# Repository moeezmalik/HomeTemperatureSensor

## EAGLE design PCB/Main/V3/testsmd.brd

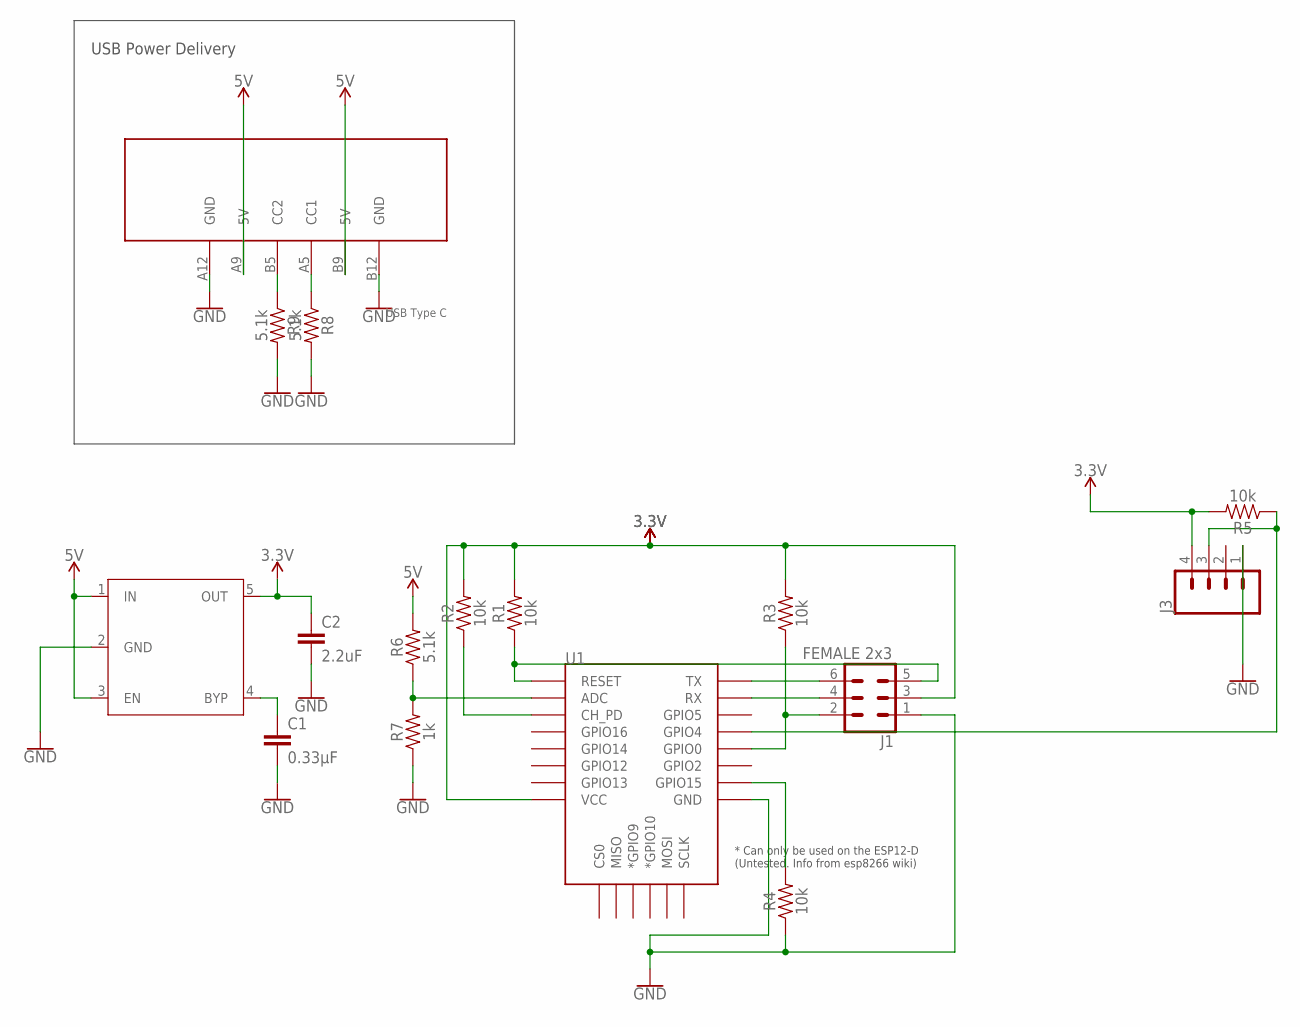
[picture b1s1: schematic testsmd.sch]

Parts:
C1: 0.33µF; 0805
C2: 2.2uF; 1206
J1: FEMALE 2x3; 2X3
J3: CONN_04; 1X04
R1, R2, R3, R4, R5: 10k; 0805
R6, R8, R9: 5.1k; 0805
R7: 1k; 0805
U1: ESP12ESMD; ESP12E-SMD
U$1: MIC5219; SOT95P280X145-5N
U$3: USBC6PIN

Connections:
3.3V: C2.1, J1.3, J3.4, R1.2, R2.2, R3.2, R5.2, U1.VCC, U$1.5 (OUT)
5V: R6.2, U$1.1 (IN), U$1.3 (EN), U$3.A9 (5V), U$3.B9 (5V)
GND: C1.2, C2.2, J1.1, J3.1, R4.1, R7.1, R8.2, R9.2, U1.GND, U$1.2 (GND), U$3.A12 (GND), U$3.B12 (GND)
unnamed: R4.2, U1.GPIO15
unnamed: J1.6, U1.TXD0 (TX)
unnamed: J1.5, R1.1, U1.RESET
unnamed: R2.1, U1.CH_PD
unnamed: J1.2, R3.1, U1.GPIO0
unnamed: J1.4, U1.RXD0 (RX)
unnamed: J3.3, R5.1, U1.GPIO4
unnamed: C1.1, U$1.4 (BYP)
unnamed: R6.1, R7.2, U1.ADC
unnamed: R9.1, U$3.B5 (CC2)
unnamed: R8.1, U$3.A5 (CC1)

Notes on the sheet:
USB Power Delivery

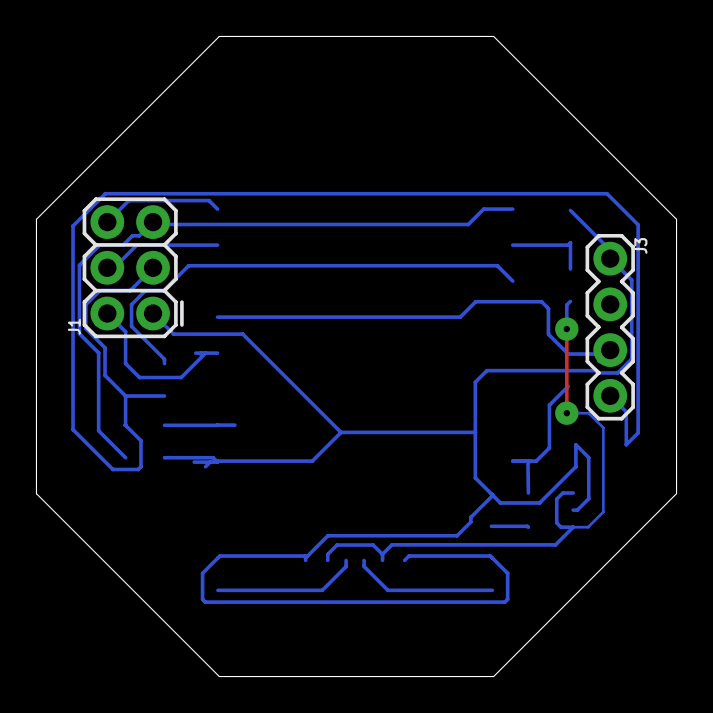
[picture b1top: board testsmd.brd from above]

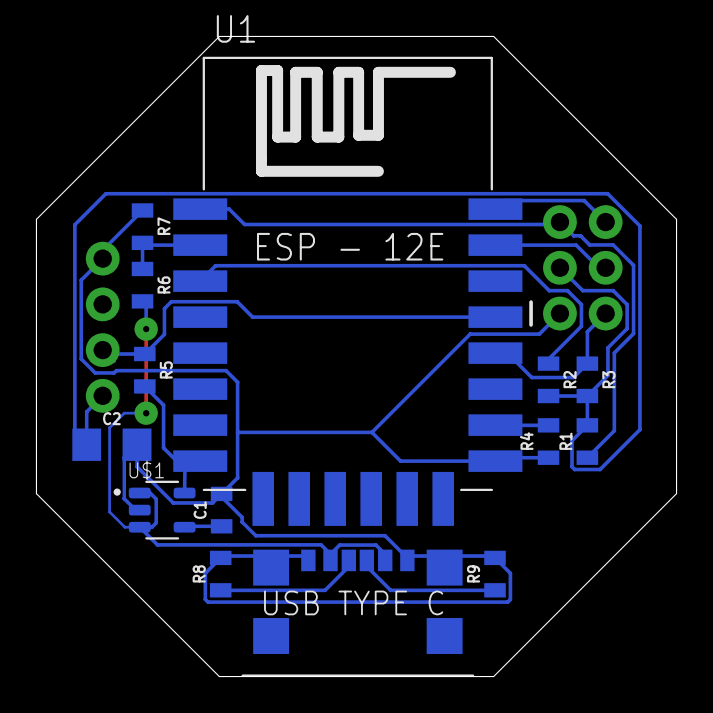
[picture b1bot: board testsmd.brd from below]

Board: 2 copper layers, 35.6 x 35.6 mm, 16 parts (14 on the bottom side), 14 nets.

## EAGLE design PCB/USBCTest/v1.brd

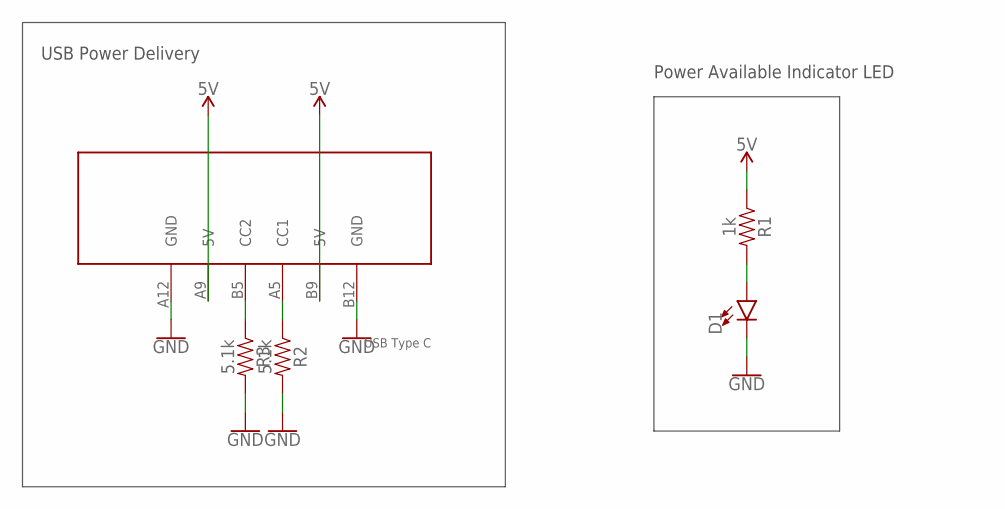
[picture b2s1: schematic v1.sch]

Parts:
D1: LED1206; LED-1206
R1: 1k; 0805
R2, R3: 5.1k; 0805
U$1: USBC6PIN

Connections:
5V: R1.1, U$1.A9 (5V), U$1.B9 (5V)
GND: D1.C, R2.2, R3.2, U$1.A12 (GND), U$1.B12 (GND)
unnamed: R3.1, U$1.B5 (CC2)
unnamed: R2.1, U$1.A5 (CC1)
unnamed: D1.A, R1.2

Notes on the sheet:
USB Power Delivery
Power Available Indicator LED

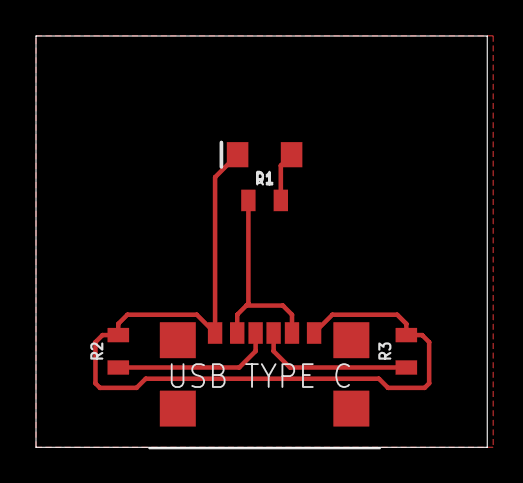
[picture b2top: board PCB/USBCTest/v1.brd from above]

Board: 2 copper layers, 25.1 x 22.9 mm, 5 parts (0 on the bottom side), 5 nets.

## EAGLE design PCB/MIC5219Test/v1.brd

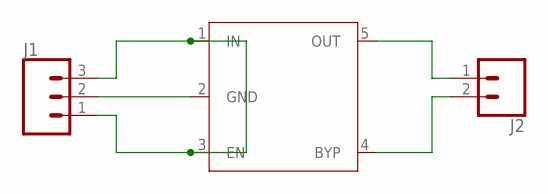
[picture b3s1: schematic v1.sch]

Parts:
J1: CONN_03; 1X03
J2: CONN_02; 1X02
U$1: MIC5219; SOT95P280X145-5N

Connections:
unnamed: J1.1, J1.3, U$1.1 (IN), U$1.3 (EN)
unnamed: J1.2, U$1.2 (GND)
unnamed: J2.1, U$1.5 (OUT)
unnamed: J2.2, U$1.4 (BYP)

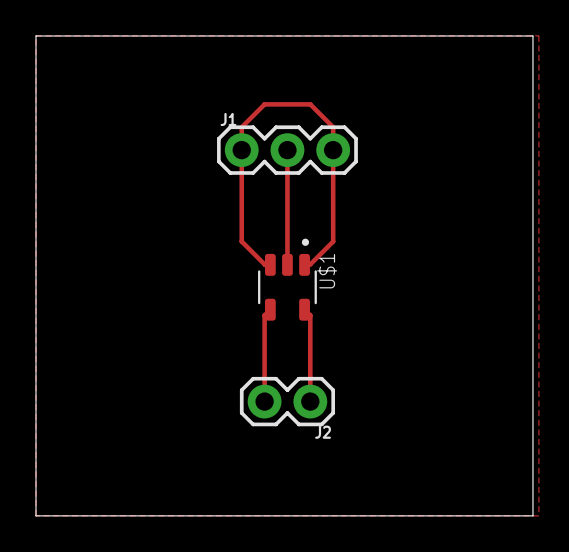
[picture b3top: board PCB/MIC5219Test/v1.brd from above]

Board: 2 copper layers, 27.6 x 26.7 mm, 3 parts (0 on the bottom side), 4 nets.

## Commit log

2019-11-14 Added Initial Files
    WiFi connection is working, switches to setup mode when saved WiFi could not be found.
2019-11-21 Test PCB for MIC5219
    Created a PCB for testing the voltage regulator that is much smaller in size and more importantly has a low dropout voltage of only 10mV at low load and 500mV at peak load. The max current output of 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
2019-11-26 Addded the OG SMD PCB Files
2019-11-26 Changed the 3.3v regulator to MIC5219
2019-11-28 File cleanup
2019-12-04 initial tests for shifting to usb type c
2019-12-04 working towards graphs
2019-12-04 Test PCB for USB Implementation
2019-12-04 test pcb for usb c
2019-12-07 .DS_Store Banished!
2019-12-07 adding and testing the add via http get feature
2019-12-09 Used HTTP GET instead of MQTT.
2019-12-11 New board revision to include USB Type - C
2019-12-11 housekeeping
2019-12-12 Changes to make design block
2019-12-12 Changing the board layout and adding capability to read V_BUS

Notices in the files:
parts and their libraries:
SparkFun-Connectors: Licensing: Creative Commons ShareAlike 4.0 International - https://creativecommons.org/licenses/by-sa/4.0
